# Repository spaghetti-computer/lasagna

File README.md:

# LASAGNA2354 (ラザニア2354)

> Project renamed from **NESPICO** to **ラザニア2354 / LASAGNA2354** (2026-10-13, working tree only). The Python package `nespico/`, the CLI, the GitHub repo name, firmware target names and older (Rev.A/B/bring-up) KiCad file names keep `nespico` / `NESPICO` for now, because renaming them would break imports, CI and existing artifacts.

A low-cost USB Famicom cartridge reader and **live-cartridge console** experiment.

The cartridge is not just a source for a ROM dump: the eventual console should drive the inserted physical cartridge's CPU and PPU buses while running the NES CPU/PPU/APU on an RP2350. The host PC or Mac handles display, audio playback, and controls.

## Project overview

```text
Physical Famicom 60-pin cartridge
               |
     74-series bus interface
     (latches / transceivers)
               |
      Raspberry Pi Pico 2 + PIO
               |
           USB Full Speed
               |
           PC / Mac host
   video, audio, controls, dumps
```

**Target hardware:** standard non-wireless Raspberry Pi Pico 2 (RP2350), 74-series logic, a real 60-pin cartridge connector and USB. The Pico 2 exposes 26 header GPIOs (GP0–GP22, GP26–GP28). For this design, GP26–GP28 are reserved for ADC0–ADC2 analog inputs; GP29 is ADC3 used by the board's VSYS monitor and is not a header GPIO. This leaves **23 digital GPIOs (GP0–GP22)**, so the earlier 27-GPIO concept must move at least four functions into external logic or be redesigned. No FPGA, HDMI shield or wireless module is planned. GPIO allocation and electrical protection are not finalized; see the [board architecture proposal](hardware/kicad/board-plan.md).

## Goals

1. **Play real cartridges.** Read PRG and CHR from the inserted cartridge during execution, support cartridge-side bank switching, CHR-RAM and mapper-generated IRQs instead of silently substituting a fully dumped ROM.
2. **Dump cartridges.** Read PRG-ROM and CHR-ROM to a host computer over USB, verify dumps, and support applicable mapper-controlled banks and cartridge save RAM.
3. **Reproduce physical-console behavior.** Keep motherboard RAM across RESET and cartridge replacement with power retained. Test tricks such as **Tennis → Super Mario Bros. World 9**. This is **not** a request for automatic hot-swap detection or live game switching; cartridge removal with power applied also needs electrical safety validation.
4. **Use the computer as the display.** Stream enough video/audio information over USB for a small PC/Mac viewer, and receive controller input from the host. USB Full Speed means raw full-frame 60fps video is not a feasible default protocol.
5. **Keep the hardware inexpensive and buildable in a quantity of two.** Prefer off-the-shelf Pico 2 boards, inexpensive standard logic and hand-assembled connectors to a custom MCU/FPGA board.

## Development approach

**Simulation first, hardware second.** The host-side simulator models approximate NTSC CPU/PPU bus demand, nominal 74-series/PIO transaction latency, overlapping requests, simplified MMC3 A12 qualification, RESET RAM retention and USB bandwidth assumptions. GitHub Actions runs the tests without any connected hardware.

The simulation is a *screening tool*, not proof that physical timing works. It does not execute actual PIO, emulate a complete 6502/PPU, validate the cartridge voltage interface, or establish real USB throughput. PPU events use classified 2-dot fetch slots from the documented rendering schedule, but do not include generated PPU addresses or rendering-state changes.

### Current status

- Host-side deterministic bus-timing simulator and 39 regression tests are present, including exhaustive five-step checks of the abstract shared-bus guard and PPU fetch-slot phase checks. The local suite and Pico SDK 2.3.1 firmware builds pass; invalid test GPIO maps are rejected before compilation. Both GitHub Actions workflows passed for commit `8f26041` on `work/rp2350-pio-bringup`.
- Firmware CI checks PIO instruction order, sample strobe side-set, loop width, and agreement between the calculated 99 instruction clocks and C constants. It builds a second test map using Pico 2 header GPIOs GP20–GP22 and GP26–GP28, and rejects duplicate, malformed, out-of-range, leading-zero, and board-reserved GPIO assignments. These are source/configuration checks, not hardware execution.
- A one-bit AHCT/LVC level-interface candidate schematic and a 35-case switch-level SPICE screen are now available under `hardware/`; the assumed cartridge release timing is not measured, so this is not electrical sign-off.
- GPIO pin map, 5V interface, physical timing, accurate NES emulator, cartridge swapping and USB video protocol remain to be validated.
- **No claim of working cartridge playback or real-device ROM dumping yet.**

### Local checks

```sh
python -m unittest discover -s tests -v
python -m nespico.cli --scanlines 262
python -m nespico.cli --sys-mhz 20 --settle-ns 160 --scanlines 1 # expected failure
python3 firmware/pio_bringup/validate_pio_source.py
```

## Development records

- [Development log (2026-10-12)](docs/journal/2026-10-12.md)
- [Development roadmap](docs/roadmap.md)
- [Simulation results](docs/benchmark-results.md)
- [PIO bring-up checkpoint](docs/pio-bringup.md)
- [Preliminary one-bit KiCad interface slice](hardware/kicad/README.md) and [Pico 2 board architecture proposal](hardware/kicad/board-plan.md)
- [Bus-turnaround SPICE screening model](hardware/spice/README.md)

## Milestones

1. CI timing simulator + executable design assumptions
2. PIO bus-pattern generator on Pico 2, measured with loopback and a logic analyzer
3. 74-series interface prototype: safe NROM PRG/CHR readback
4. USB dumper with validation and mapper-aware read/write
5. Real-cart CPU+PPU operation, host video/audio and input
6. RAM-preserving RESET, cartridge replacement tests and MMC1/MMC3

See [architecture notes](docs/architecture.md) and [simulation results](docs/benchmark-results.md). The extra pipeline tests model the CPU/PPU work required to prepare addresses; they show that nominal bus-only timing success is not sufficient.

The first Pico SDK / PIO firmware target is a **test-only dual-lane GPIO loopback** under `firmware/pio_bringup/`. It is intentionally not a cartridge bus driver; see its [build and safety instructions](firmware/pio_bringup/README.md). A board-specific pinout and real logic-analyzer measurements are still required before freezing a cartridge interface or releasing PCB files for fabrication.

Reference documentation: [NESdev cartridge connector](https://www.nesdev.org/wiki/Cartridge_connector), [PPU rendering](https://www.nesdev.org/wiki/PPU_rendering), [MMC3](https://www.nesdev.org/wiki/MMC3), [RP2350](https://www.raspberrypi.com/documentation/microcontrollers/silicon.html).

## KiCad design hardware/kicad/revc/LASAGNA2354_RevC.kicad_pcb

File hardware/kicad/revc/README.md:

# LASAGNA2354 (ラザニア2354) Rev.C KiCad project (PROPOSAL, NOT FAB-READY unless the status below says so)

The board uses a bare RP2354B and 7 AHCT logic ICs. Everything the board drives toward the cart is at 5 V.
Design notes are in ../revc-plan.md, section 2b.

Regenerate:
```
python3 gen_sch.py
python3 gen_pcb.py
# Specctra DSN -> Freerouting -> SES import (see the status below)
python3 export_fab.py
```

## Unverified / open
- Famicom slot footprint: a 2x30 2.54 mm placeholder. The real slot mechanics are not verified.
- RCA footprint is custom and not verified. Pad headers J4/J5 use a generic 1x7 pinout and are 3.3 V only (driven by U10 MCP23017). The Grove J9 footprint is a JST PH stand-in (unverified).
- L1: uses a Murata DFE201610P land as a stand-in for the Abracon AOTA-B201610S3R3-101-T.
  The land and the polarity dot orientation (the HDG says polarity matters) still need checking.
  LCSC showed stock 0 at check.
- QFN-80 footprint: the KiCad EP is 3.4x3.4 mm. Check it against the RP2350 datasheet package drawing.
  Pins 60 and 76 = IOVDD come from the pinout figure, because the power table omitted them.
- USB-C placement relative to the board edge must be checked in the 3D view.
- Power-down sequencing (+3V3 vs +5V_CART decay) has not been analysed.
- Freerouting does not enforce F.Cu vertical / B.Cu horizontal. That is intent only.
- Cart audio pins 45/46 are NC.

## Aesthetic pass / routing guidelines for Leo (Quilter or hand routing)
- Fab: BLACK mask, WHITE silk, HASL lead-free. See FAB_NOTES.md.
- Locked layout: row A = A1..A7 (U2 U4 U6 | U8 | U7 U5 U3), 13 mm pitch, all at the same rotation.
  CPU and PPU sides mirror exactly about x=50 (error 0.00 mm). U8 is on the centreline.
  The 100 nF decaps follow each IC's pin 20, so they are not mirrored.
- 33R AD series arrays: R10..R17 (CPU) and R20..R27 (PPU), 2.0 mm pitch at y=31, centred under columns 2 and 6, mirrored.
- Front silk: grid font 1.2 mm only (A1..A7, column numbers, row letter A, CPU/PPU) plus one title "LASAGNA2354 Rev.C".
  Refdes are on F.Fab. The back silk carries only LASAGNA2354 REV.C / MADE IN KOBE / JLCJLCJLCJLC and the TP labels; the refdes table is in FAB_NOTES.md.
- Pour: GND on B.Cu only. Do not pour on F.Cu.
- Routing style (intent; not enforced by DRC):
  - Run the buses as bundles at a constant pitch, with 45-degree bends only (no 90-degree corners).
  - F.Cu mostly vertical, B.Cu mostly horizontal.
  - Put vias in neat rows, one row per bus, at the layer change. Keep them out of the slot keepout and the crystal area.
  - Keep B.Cu breaks in the GND pour short so the bottom plane stays continuous.

## J8 removed -> test points
The J8 2x20 measurement header is gone. It is replaced by 24 THT test pads (2.0/1.0 mm, B side) in one row. See FAB_NOTES.md for the TP table.

## Pads via I2C (MCP23017) + Grove
Both pads (J4/J5) are read through U10 MCP23017 on I2C0 (GPIO44/45). U10 and the pads run at 3.3 V.
Grove J9 shares the bus. GPIO46/47 are spare, on TP G46/G47. See ../revc-plan.md section 2f.

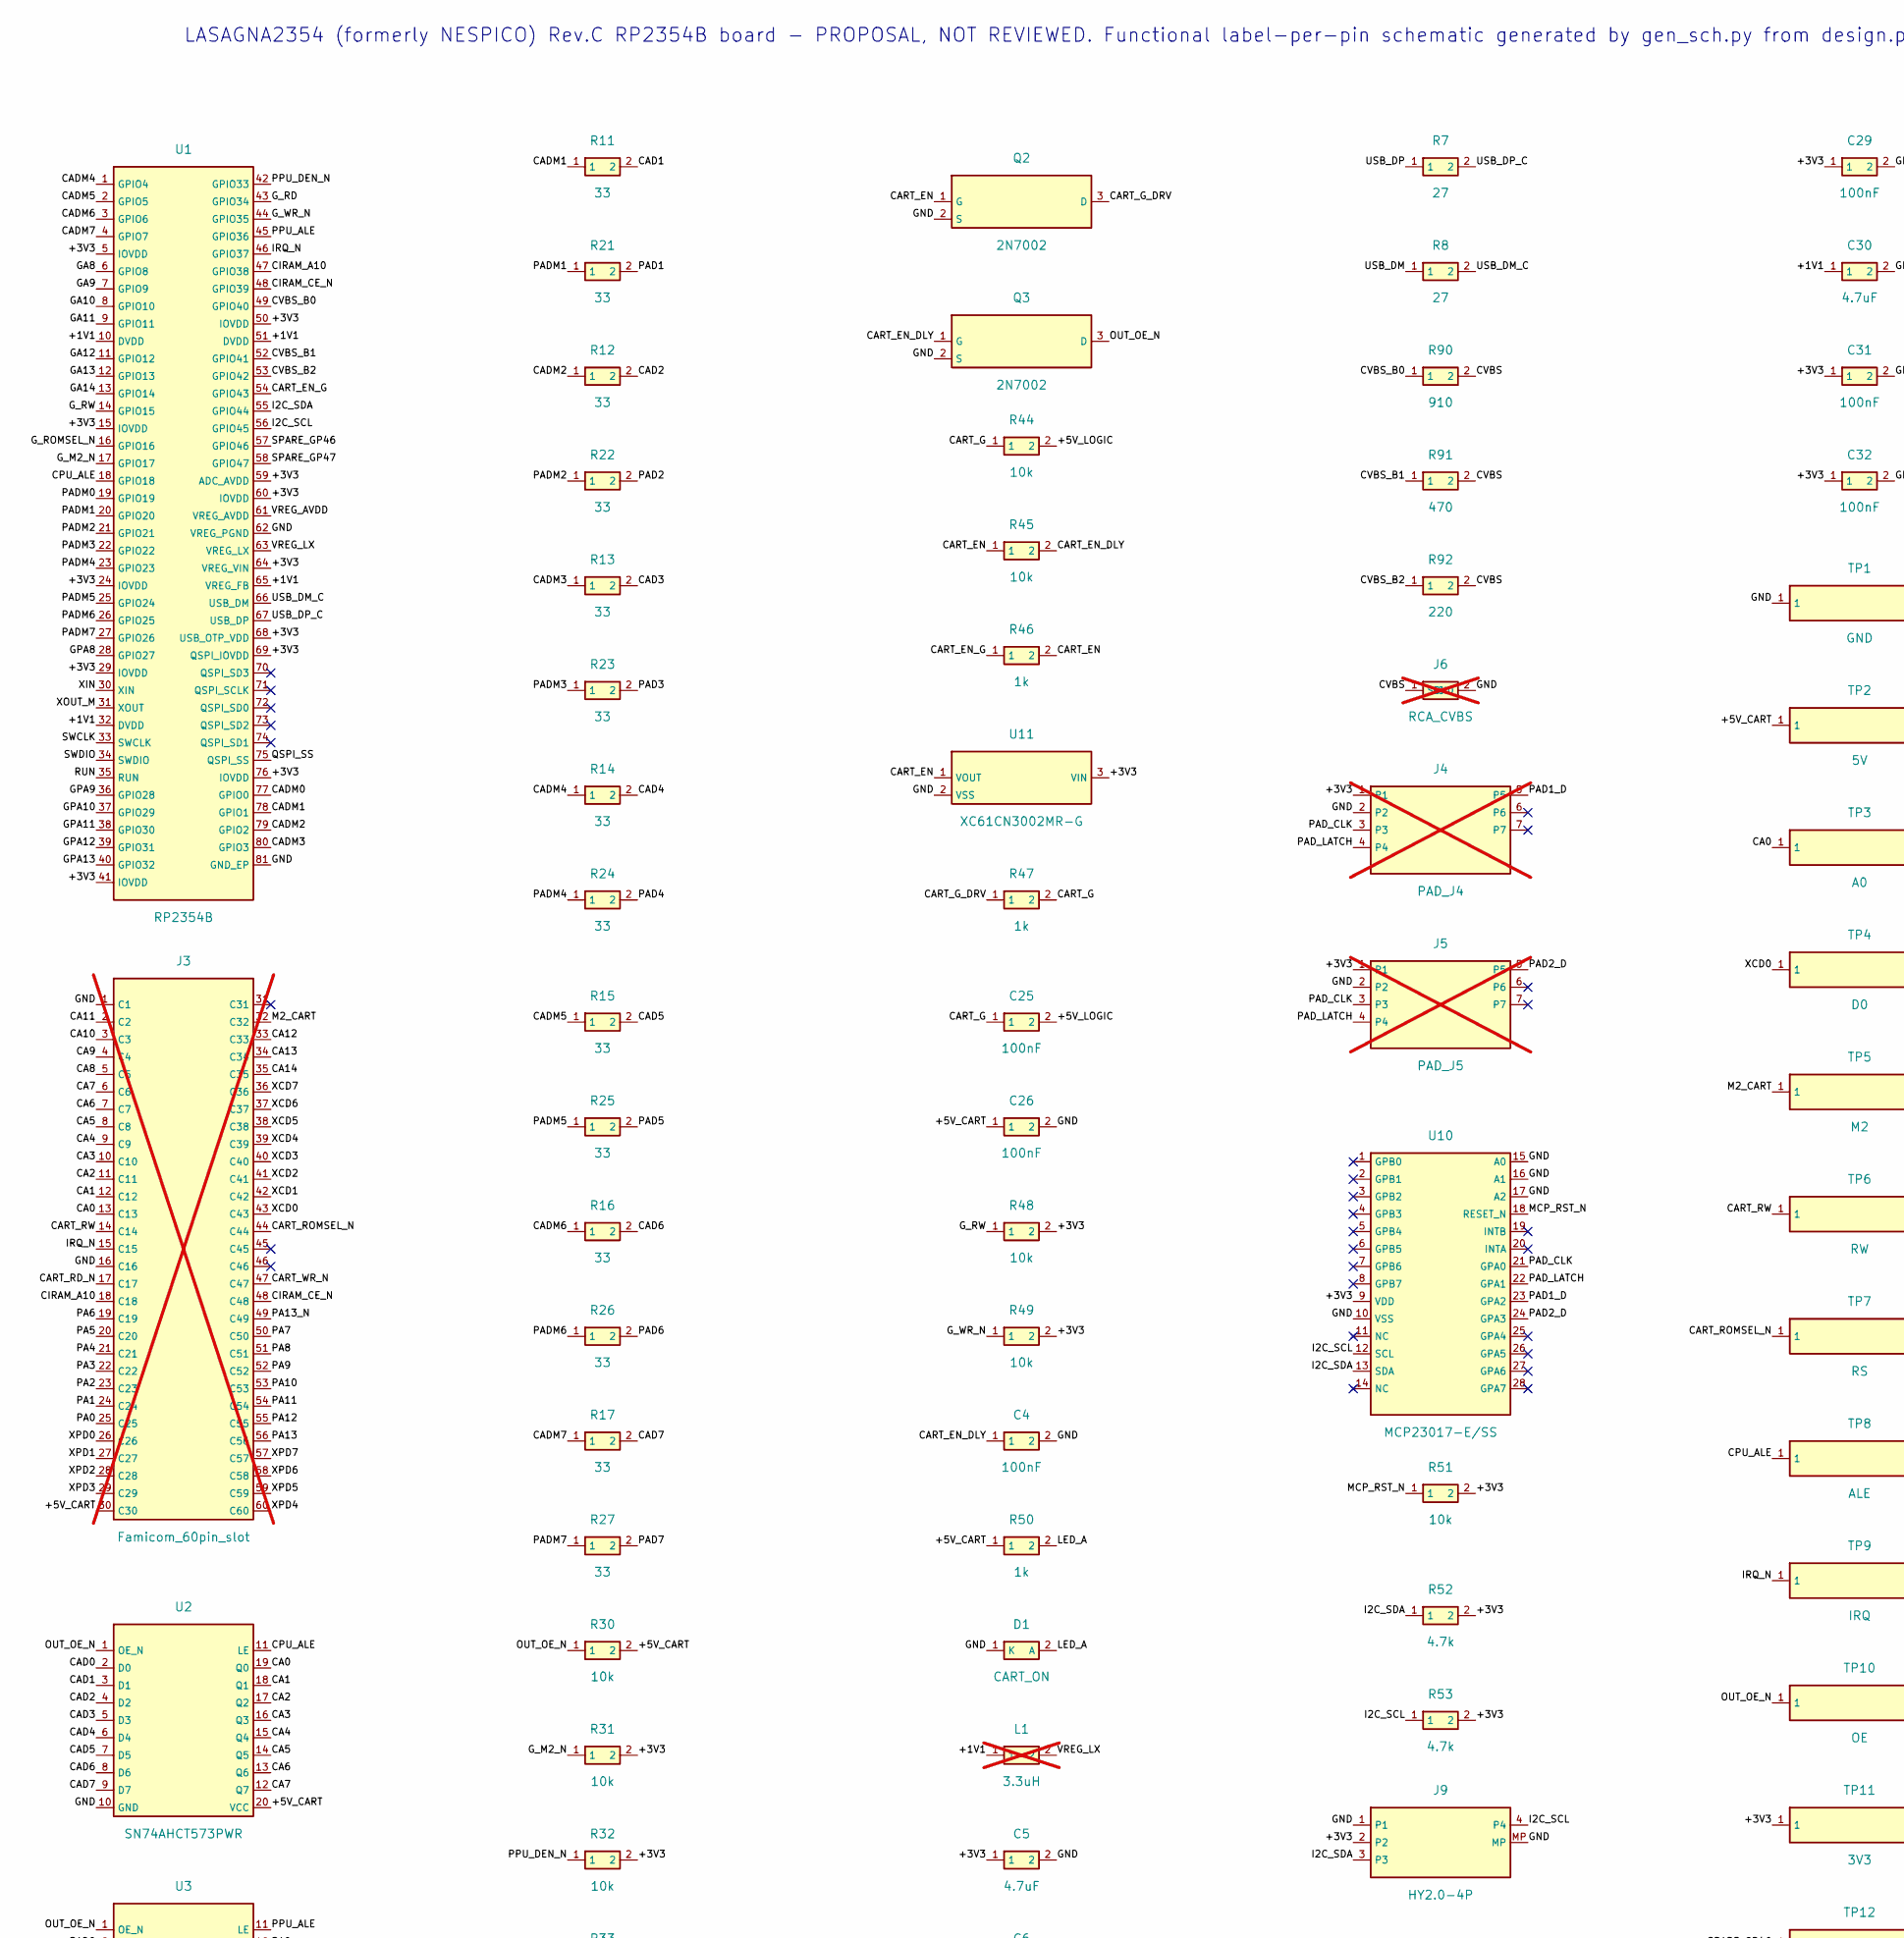
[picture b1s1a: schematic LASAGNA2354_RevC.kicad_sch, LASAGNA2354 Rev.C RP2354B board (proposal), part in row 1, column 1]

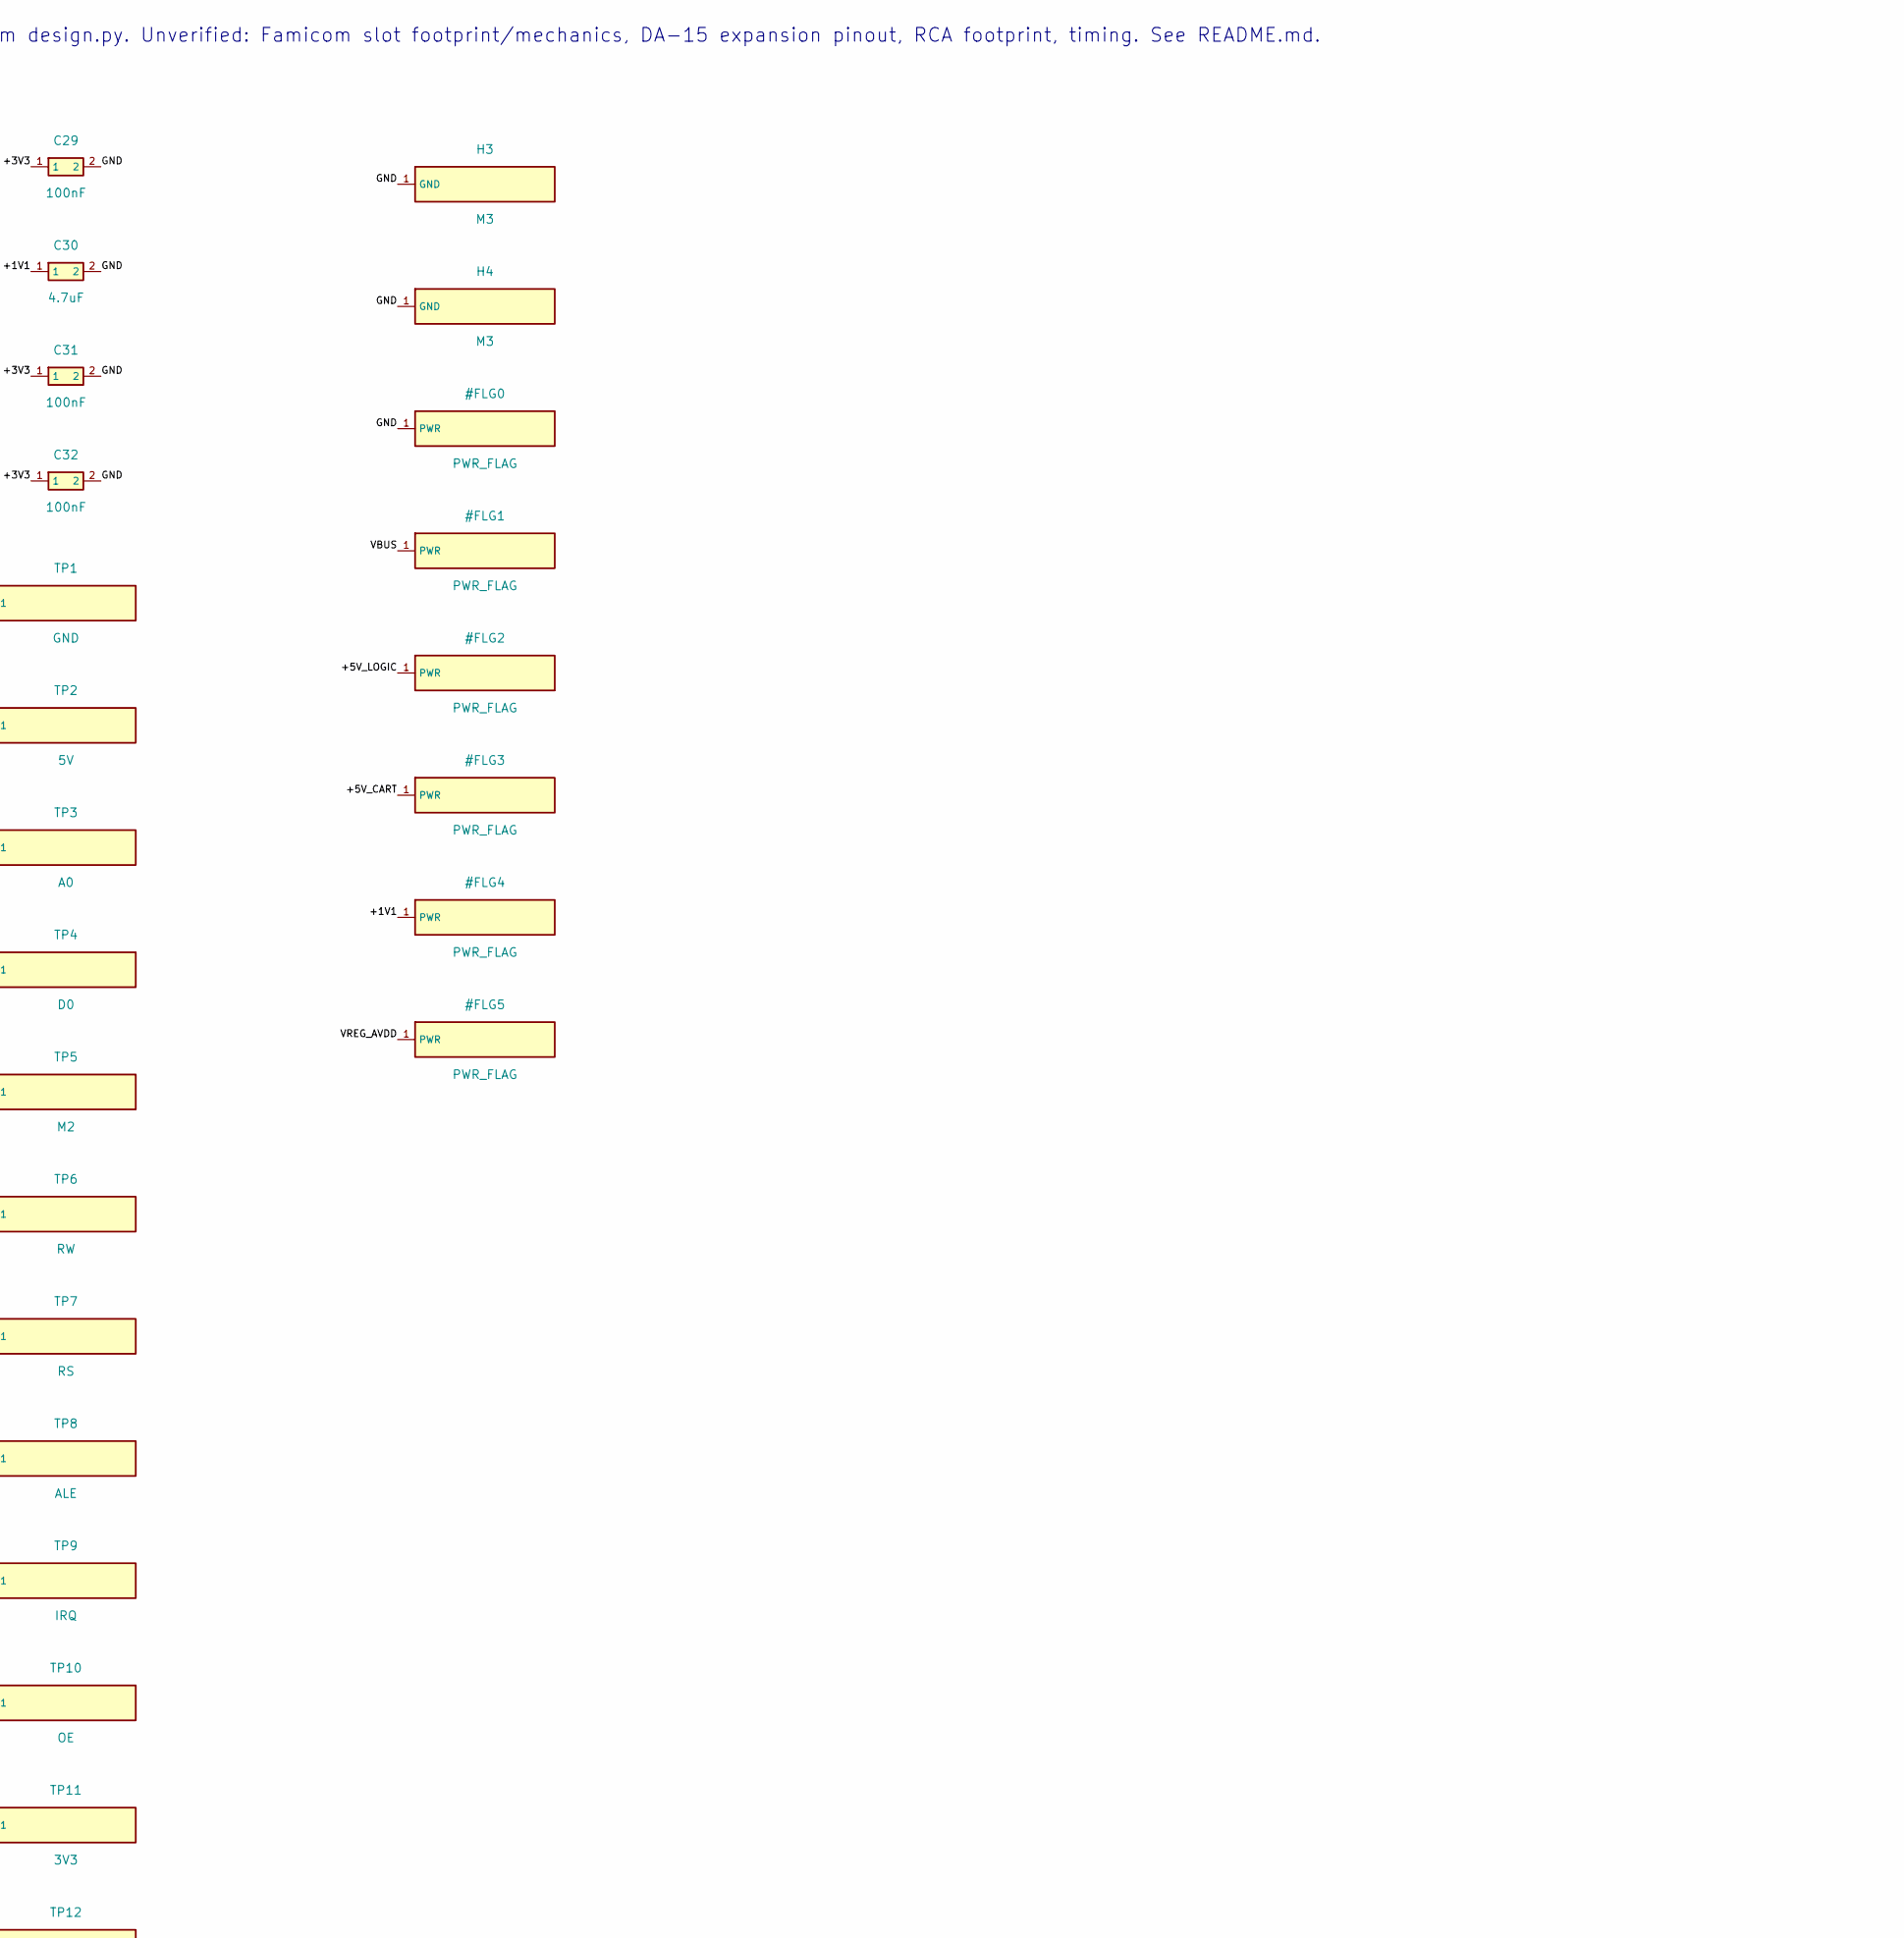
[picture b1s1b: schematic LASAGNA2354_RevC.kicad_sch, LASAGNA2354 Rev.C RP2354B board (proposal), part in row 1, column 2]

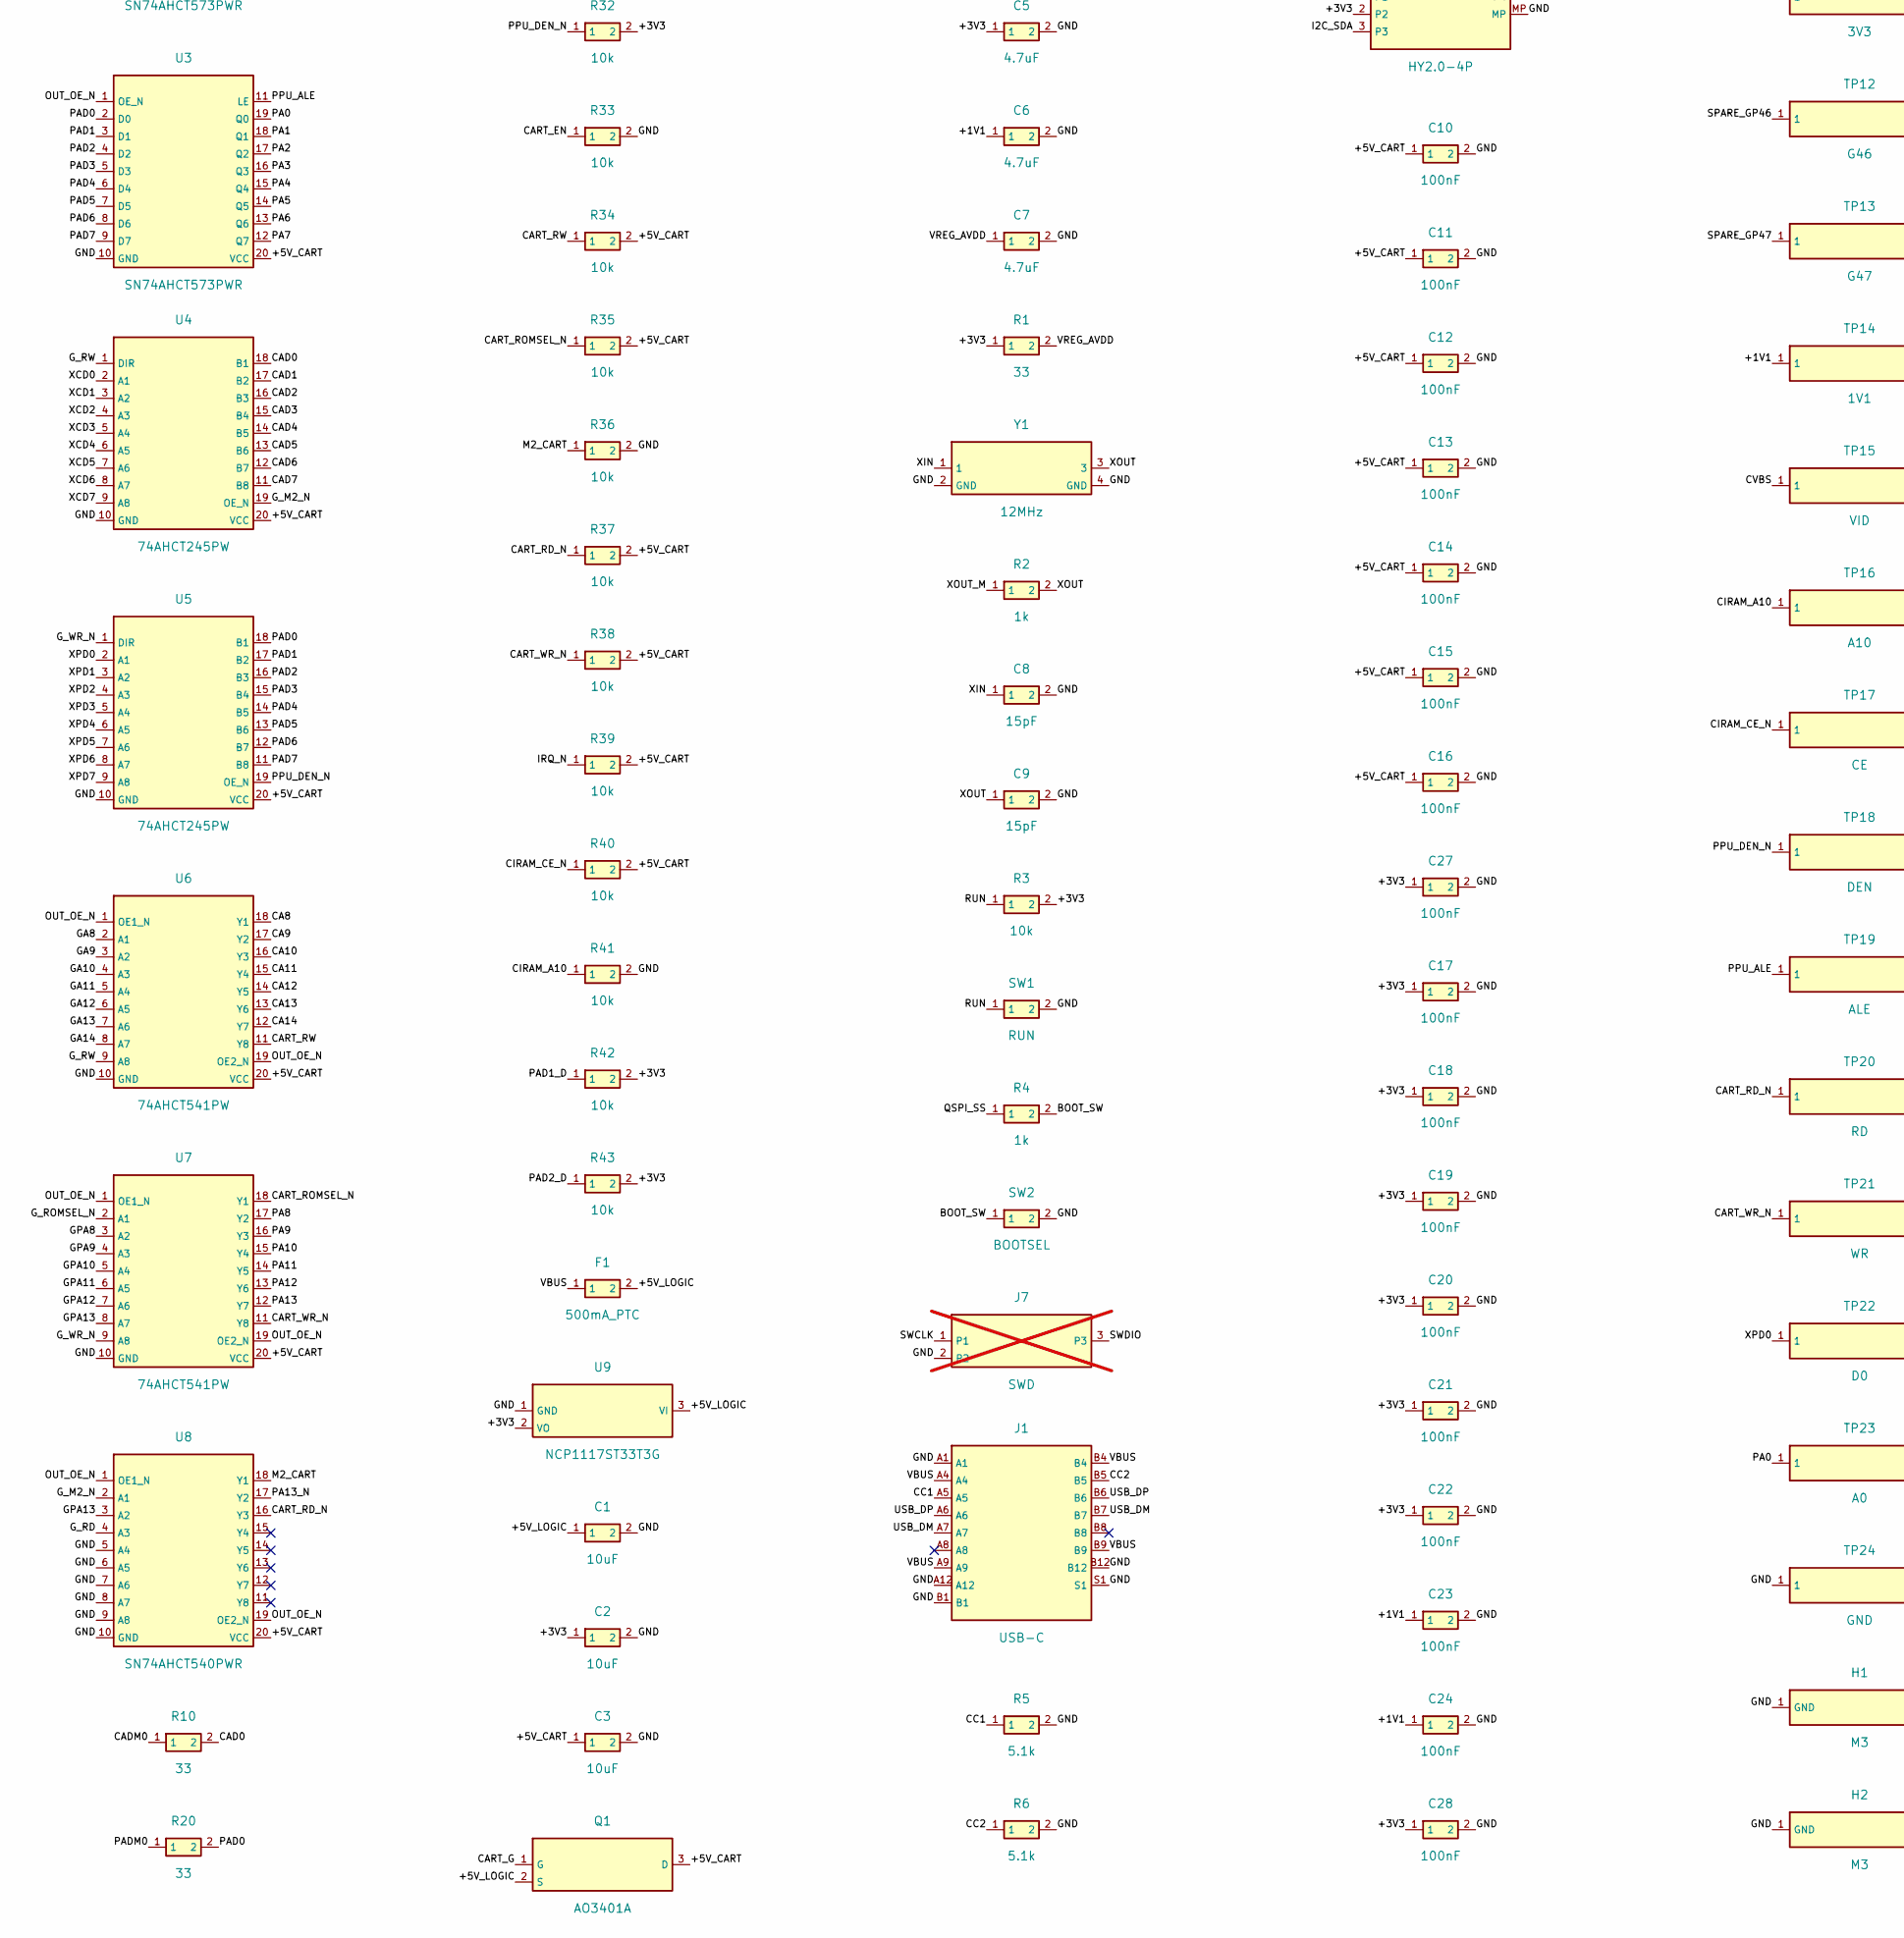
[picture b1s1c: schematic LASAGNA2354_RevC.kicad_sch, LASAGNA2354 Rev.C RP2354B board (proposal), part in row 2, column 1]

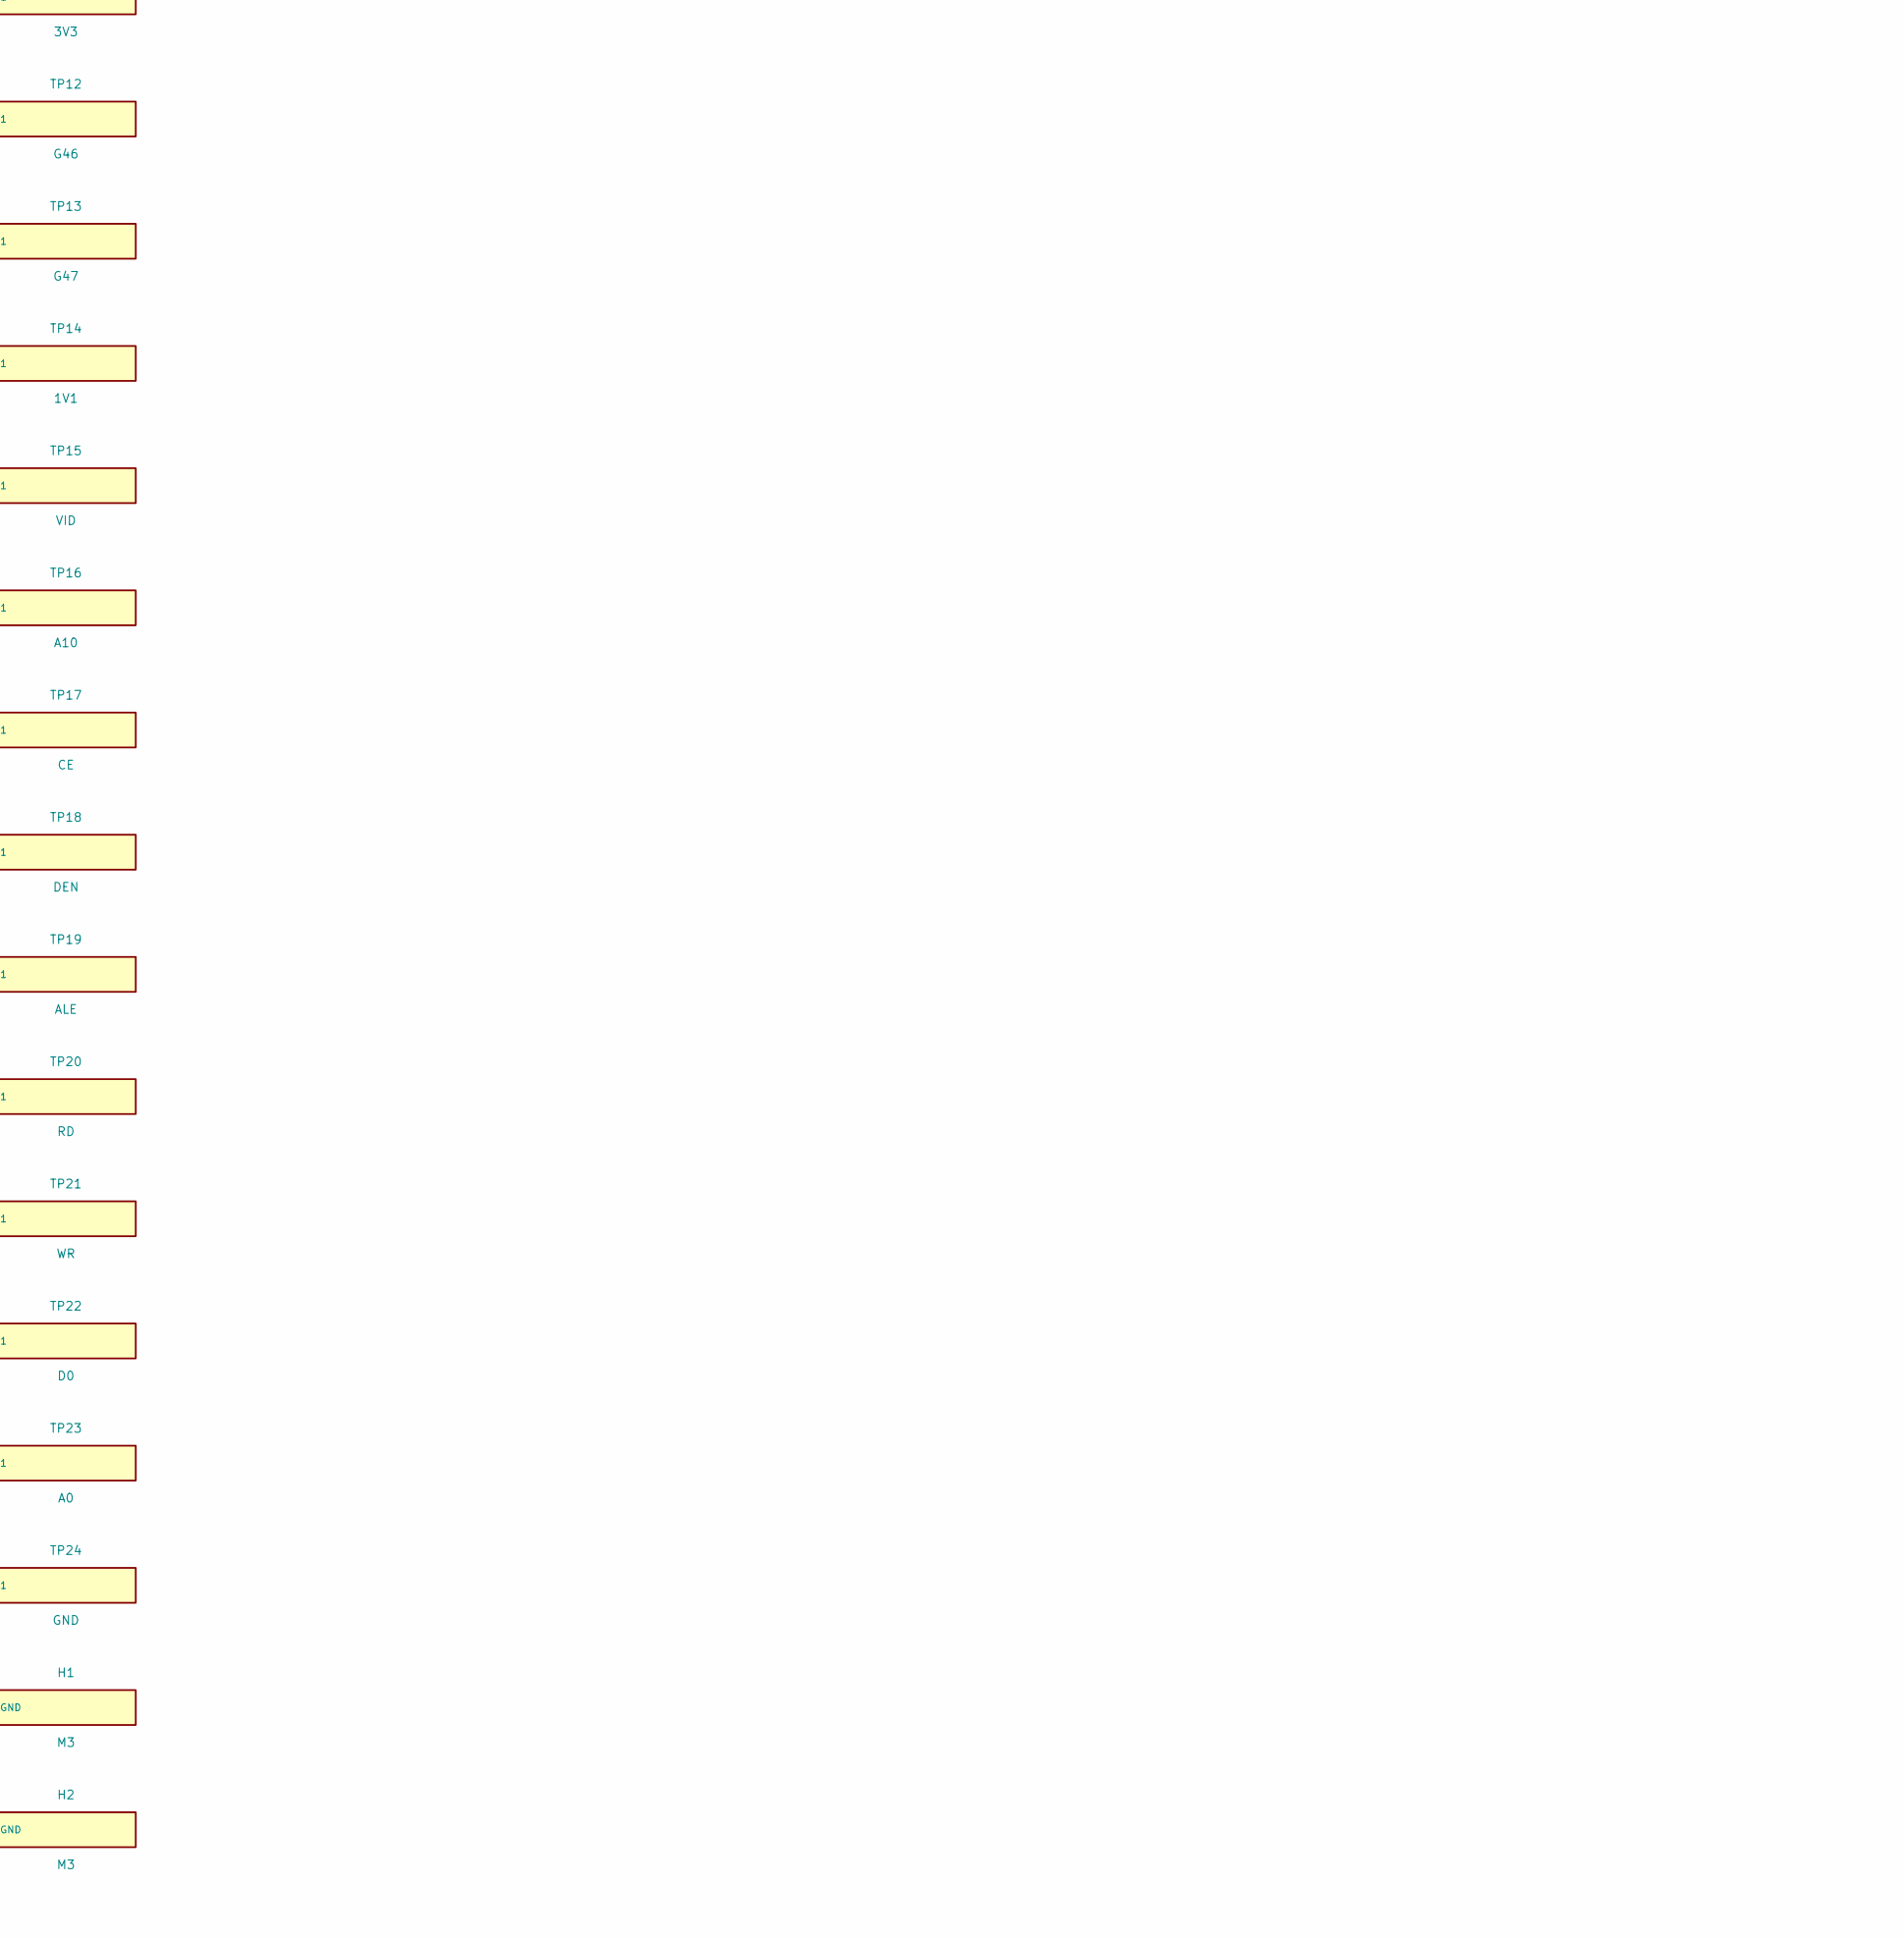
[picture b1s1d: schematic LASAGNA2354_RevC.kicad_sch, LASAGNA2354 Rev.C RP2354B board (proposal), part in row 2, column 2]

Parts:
C1, C2, C3: 10uF; C_0805_2012Metric; MPN 10uF; LCSC C15850
C4, C10, C11, C12, C13, C14, C15, C16, C17, C18, C19, C20, C21, C22, C23, C24, C25, C26, C27, C28, C31, C32: 100nF; C_0603_1608Metric; MPN 100nF; LCSC C14663
C5, C6, C7, C30: 4.7uF; RPi_C_1005_wide; MPN 4.7uF-0402; LCSC C23733
C8, C9: 15pF; RPi_C_1005_wide; MPN 15pF-0402; LCSC C1548
C29: 100nF; RPi_C_1005_wide; MPN 100nF-0402; LCSC C1525
D1: CART_ON; LED_0603_1608Metric; MPN LED_G; LCSC C2286
F1: 500mA_PTC; Fuse_1206_3216Metric; MPN SMD1206-050-6; LCSC C46641012
H1, H2, H3, H4: M3; MountingHole_3.2mm_M3_Pad; LCSC_Status no LCSC part
J1: USB-C; USB_C_Receptacle_HRO_TYPE-C-31-M-12; MPN TYPE-C-31-M-12; LCSC C165948
J3: Famicom_60pin_slot; Hirose_CR22A-60D-2.54DS; MPN CR22A-60D-2.54DS(70); LCSC_Status hand-assembly / not PCBA; not fitted
J4: PAD_J4; PinHeader_1x07_P2.54mm_Vertical; LCSC_Status hand-assembly / not PCBA; not fitted
J5: PAD_J5; PinHeader_1x07_P2.54mm_Vertical; LCSC_Status hand-assembly / not PCBA; not fitted
J6: RCA_CVBS; RCA_Avvicon_MJ-526; MPN MJ-526-Y; LCSC_Status hand-assembly / not PCBA; not fitted
J7: SWD; PinHeader_1x03_P2.54mm_Vertical; LCSC_Status hand-assembly / not PCBA; not fitted
J9: HY2.0-4P; JST_PH_S4B-PH-SM4-TB_1x04-1MP_P2.00mm_Horizontal; MPN HY2.0-4P-WT; LCSC C722729
L1: 3.3uH; RPi_AOTA-B201610S3R3-101-T; MPN AOTA-B201610S3R3-101-T; LCSC C42411119; not fitted
Q1: AO3401A; SOT-23; MPN AO3401A; LCSC C15127
Q2, Q3: 2N7002; SOT-23; MPN 2N7002; LCSC C8545
R1: 33; RPi_R_1005; MPN 33R-0402; LCSC C25105
R2: 1k; RPi_R_1005; MPN 1k-0402; LCSC C11702
R3, R30, R31, R32, R33, R34, R35, R36, R37, R38, R39, R40, R41, R42, R43, R44, R45, R48, R49, R51: 10k; R_0603_1608Metric; MPN 10k; LCSC C25804
R4, R46, R47, R50: 1k; R_0603_1608Metric; MPN 1k; LCSC C21190
R5, R6: 5.1k; R_0603_1608Metric; MPN 5.1k; LCSC C23186
R7, R8: 27; RPi_R_1005; MPN 27R-0402; LCSC C25100
R10, R11, R12, R13, R14, R15, R16, R17, R20, R21, R22, R23, R24, R25, R26, R27: 33; R_0603_1608Metric; MPN 33; LCSC C23140
R52, R53: 4.7k; R_0603_1608Metric; MPN 4.7k; LCSC C23162
R90: 910; R_0603_1608Metric; MPN 910; LCSC C23264
R91: 470; R_0603_1608Metric; MPN 470; LCSC C23179
R92: 220; R_0603_1608Metric; MPN 220; LCSC C22962
SW1: RUN; SW_Push_1P1T_XKB_TS-1187A; MPN TS-1187A-B-A-B; LCSC C318884
SW2: BOOTSEL; SW_Push_1P1T_XKB_TS-1187A; MPN TS-1187A-B-A-B; LCSC C318884
TP1, TP24: GND; TestPoint_THTPad_D2.0mm_Drill1.0mm; LCSC_Status no LCSC part
TP2: 5V; TestPoint_THTPad_D2.0mm_Drill1.0mm; LCSC_Status no LCSC part
TP3, TP23: A0; TestPoint_THTPad_D2.0mm_Drill1.0mm; LCSC_Status no LCSC part
TP4, TP22: D0; TestPoint_THTPad_D2.0mm_Drill1.0mm; LCSC_Status no LCSC part
TP5: M2; TestPoint_THTPad_D2.0mm_Drill1.0mm; LCSC_Status no LCSC part
TP6: RW; TestPoint_THTPad_D2.0mm_Drill1.0mm; LCSC_Status no LCSC part
TP7: RS; TestPoint_THTPad_D2.0mm_Drill1.0mm; LCSC_Status no LCSC part
TP8, TP19: ALE; TestPoint_THTPad_D2.0mm_Drill1.0mm; LCSC_Status no LCSC part
TP9: IRQ; TestPoint_THTPad_D2.0mm_Drill1.0mm; LCSC_Status no LCSC part
TP10: OE; TestPoint_THTPad_D2.0mm_Drill1.0mm; LCSC_Status no LCSC part
TP11: 3V3; TestPoint_THTPad_D2.0mm_Drill1.0mm; LCSC_Status no LCSC part
TP12: G46; TestPoint_THTPad_D2.0mm_Drill1.0mm; LCSC_Status no LCSC part
TP13: G47; TestPoint_THTPad_D2.0mm_Drill1.0mm; LCSC_Status no LCSC part
TP14: 1V1; TestPoint_THTPad_D2.0mm_Drill1.0mm; LCSC_Status no LCSC part
TP15: VID; TestPoint_THTPad_D2.0mm_Drill1.0mm; LCSC_Status no LCSC part
TP16: A10; TestPoint_THTPad_D2.0mm_Drill1.0mm; LCSC_Status no LCSC part
TP17: CE; TestPoint_THTPad_D2.0mm_Drill1.0mm; LCSC_Status no LCSC part
TP18: DEN; TestPoint_THTPad_D2.0mm_Drill1.0mm; LCSC_Status no LCSC part
TP20: RD; TestPoint_THTPad_D2.0mm_Drill1.0mm; LCSC_Status no LCSC part
TP21: WR; TestPoint_THTPad_D2.0mm_Drill1.0mm; LCSC_Status no LCSC part
U1: RP2354B; QFN-80-1EP_10x10mm_P0.4mm_EP3.4x3.4mm; MPN RP2354B; LCSC C39843328
U2, U3: SN74AHCT573PWR; TSSOP-20_4.4x6.5mm_P0.65mm; MPN SN74AHCT573PWR; LCSC C141311
U4, U5: 74AHCT245PW; TSSOP-20_4.4x6.5mm_P0.65mm; MPN 74AHCT245PW,118; LCSC C173388
U6, U7: 74AHCT541PW; TSSOP-20_4.4x6.5mm_P0.65mm; MPN 74AHCT541PW,118; LCSC C84548
U8: SN74AHCT540PWR; TSSOP-20_4.4x6.5mm_P0.65mm; MPN SN74AHCT540PWR; LCSC C7626
U9: NCP1117ST33T3G; SOT-223-3_TabPin2; MPN NCP1117ST33T3G; LCSC C26537
U10: MCP23017-E/SS; SSOP-28_5.3x10.2mm_P0.65mm; MPN MCP23017-E/SS; LCSC C506653
U11: XC61CN3002MR-G; SOT-23; MPN XC61CN3002MR-G; LCSC C2456348
Y1: 12MHz; RPi_XTAL_3225-4; MPN ABM8-272-T3; LCSC C20625731

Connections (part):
/+1V1: C6.1, C23.1, C24.1, C30.1, L1.1, TP14.1, U1.10 (DVDD), U1.32 (DVDD), U1.51 (DVDD), U1.65 (VREG_FB)
/+3V3: C2.1, C5.1, C17.1, C18.1, C19.1, C20.1, C21.1, C22.1, C27.1, C28.1, C29.1, C31.1, C32.1, J4.1, J5.1, J9.2, R1.1, R3.2, R31.2, R32.2, R42.2, R43.2, R48.2, R49.2, R51.2, R52.2, R53.2, TP11.1, U1.5 (IOVDD), U1.15 (IOVDD), U1.24 (IOVDD), U1.29 (IOVDD), U1.41 (IOVDD), U1.50 (IOVDD), U1.59 (ADC_AVDD), U1.60 (IOVDD), U1.64 (VREG_VIN), U1.68 (USB_OTP_VDD), U1.69 (QSPI_IOVDD), U1.76 (IOVDD), U9.2 (VO), U10.9 (VDD), U11.3 (VIN)
/+5V_CART: C3.1, C10.1, C11.1, C12.1, C13.1, C14.1, C15.1, C16.1, C26.1, J3.30 (C30), Q1.3 (D), R30.2, R34.2, R35.2, R37.2, R38.2, R39.2, R40.2, R50.1, TP2.1, U2.20 (VCC), U3.20 (VCC), U4.20 (VCC), U5.20 (VCC), U6.20 (VCC), U7.20 (VCC), U8.20 (VCC)
/+5V_LOGIC: C1.1, C25.2, F1.2, Q1.2 (S), R44.2, U9.3 (VI)
/BOOT_SW: R4.2, SW2.1
/CA0: J3.13 (C13), TP3.1, U2.19 (Q0)
/CA1: J3.12 (C12), U2.18 (Q1)
/CA2: J3.11 (C11), U2.17 (Q2)
/CA3: J3.10 (C10), U2.16 (Q3)
/CA4: J3.9 (C9), U2.15 (Q4)
/CA5: J3.8 (C8), U2.14 (Q5)
/CA6: J3.7 (C7), U2.13 (Q6)
/CA7: J3.6 (C6), U2.12 (Q7)
/CA8: J3.5 (C5), U6.18 (Y1)
/CA9: J3.4 (C4), U6.17 (Y2)
/CA10: J3.3 (C3), U6.16 (Y3)
/CA11: J3.2 (C2), U6.15 (Y4)
/CA12: J3.33 (C33), U6.14 (Y5)
/CA13: J3.34 (C34), U6.13 (Y6)
/CA14: J3.35 (C35), U6.12 (Y7)
/CAD0: R10.2, U2.2 (D0), U4.18 (B1)
/CAD1: R11.2, U2.3 (D1), U4.17 (B2)
/CAD2: R12.2, U2.4 (D2), U4.16 (B3)
/CAD3: R13.2, U2.5 (D3), U4.15 (B4)
/CAD4: R14.2, U2.6 (D4), U4.14 (B5)
/CAD5: R15.2, U2.7 (D5), U4.13 (B6)
/CAD6: R16.2, U2.8 (D6), U4.12 (B7)
/CAD7: R17.2, U2.9 (D7), U4.11 (B8)
/CADM0: R10.1, U1.77 (GPIO0)
/CADM1: R11.1, U1.78 (GPIO1)
/CADM2: R12.1, U1.79 (GPIO2)
/CADM3: R13.1, U1.80 (GPIO3)
/CADM4: R14.1, U1.1 (GPIO4)
/CADM5: R15.1, U1.2 (GPIO5)
/CADM6: R16.1, U1.3 (GPIO6)
/CADM7: R17.1, U1.4 (GPIO7)
/CART_EN: Q2.1 (G), R33.1, R45.1, R46.2, U11.1 (VOUT)
/CART_EN_DLY: C4.1, Q3.1 (G), R45.2
/CART_EN_G: R46.1, U1.54 (GPIO43)
/CART_G: C25.1, Q1.1 (G), R44.1, R47.2
/CART_G_DRV: Q2.3 (D), R47.1
/CART_RD_N: J3.17 (C17), R37.1, TP20.1, U8.16 (Y3)
/CART_ROMSEL_N: J3.44 (C44), R35.1, TP7.1, U7.18 (Y1)
/CART_RW: J3.14 (C14), R34.1, TP6.1, U6.11 (Y8)
/CART_WR_N: J3.47 (C47), R38.1, TP21.1, U7.11 (Y8)
/CC1: J1.A5, R5.1
/CC2: J1.B5, R6.1
/CIRAM_A10: J3.18 (C18), R41.1, TP16.1, U1.47 (GPIO38)
/CIRAM_CE_N: J3.48 (C48), R40.1, TP17.1, U1.48 (GPIO39)
/CPU_ALE: TP8.1, U1.18 (GPIO18), U2.11 (LE)
/CVBS: J6.1 (SIG), R90.2, R91.2, R92.2, TP15.1
/CVBS_B0: R90.1, U1.49 (GPIO40)
/CVBS_B1: R91.1, U1.52 (GPIO41)
/CVBS_B2: R92.1, U1.53 (GPIO42)
/GA8: U1.6 (GPIO8), U6.2 (A1)
/GA9: U1.7 (GPIO9), U6.3 (A2)
/GA10: U1.8 (GPIO10), U6.4 (A3)
/GA11: U1.9 (GPIO11), U6.5 (A4)
/GA12: U1.11 (GPIO12), U6.6 (A5)
/GA13: U1.12 (GPIO13), U6.7 (A6)
/GA14: U1.13 (GPIO14), U6.8 (A7)
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
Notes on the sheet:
LASAGNA2354 (formerly NESPICO) Rev.C RP2354B board - PROPOSAL, NOT REVIEWED. Functional label-per-pin schematic generated by gen_sch.py from design.py. Unverified: Famicom slot footprint/mechanics, DA-15 expansion pinout, RCA footprint, timing. See README.md.

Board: 2 copper layers, 141 parts (24 on the bottom side), 149 nets, no tracks yet.

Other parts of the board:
FID1, FID2, FID3: Fiducial_1mm_Mask2mm

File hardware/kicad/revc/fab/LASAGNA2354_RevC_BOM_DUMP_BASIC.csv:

Comment,Designator,Footprint,LCSC Part #
100nF,"C10,C11,C12,C13,C14,C15,C16,C17,C18,C19,C20,C21,C22,C23,C24,C25,C26,C28,C31,C32,C4",C_0603_1608Metric,C14663
100nF,C29,RPi_C_1005_wide,C1525
10k,"R3,R30,R31,R32,R33,R34,R35,R36,R37,R38,R39,R40,R41,R44,R45,R48,R49",R_0603_1608Metric,C25804
10uF,"C1,C2,C3",C_0805_2012Metric,C15850
15pF,"C8,C9",RPi_C_1005_wide,C1548
1k,R2,RPi_R_1005,C11702
1k,"R4,R46,R47,R50",R_0603_1608Metric,C21190
2N7002,"Q2,Q3",SOT-23,C8545
33,R1,RPi_R_1005,C25105
33,"R10,R11,R12,R13,R14,R15,R16,R17,R20,R21,R22,R23,R24,R25,R26,R27",R_0603_1608Metric,C23140
4.7uF,"C30,C5,C6,C7",RPi_C_1005_wide,C23733
5.1k,"R5,R6",R_0603_1608Metric,C23186
AO3401A,Q1,SOT-23,C15127
BOOTSEL,SW2,SW_Push_1P1T_XKB_TS-1187A,C318884
CART_ON,D1,LED_0603_1608Metric,C2286
RUN,SW1,SW_Push_1P1T_XKB_TS-1187A,C318884
